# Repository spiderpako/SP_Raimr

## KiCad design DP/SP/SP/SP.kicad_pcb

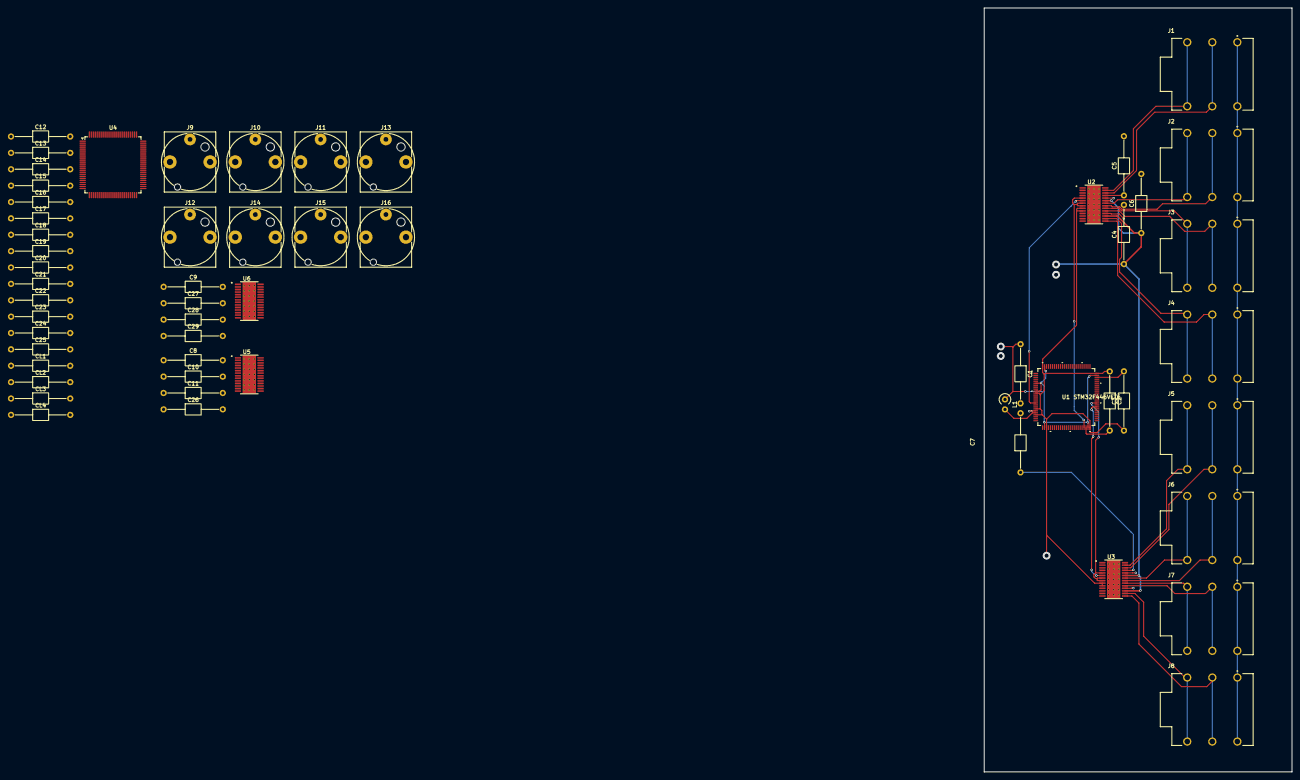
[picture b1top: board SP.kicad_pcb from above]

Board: 2 copper layers, 78.0 x 193.6 mm, 56 parts (0 on the bottom side), 60 nets.

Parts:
C1, C4, C6, C9, C10, C11, C12, C15, C16, C17, C18, C19, C20, C21, C23, C25, C26, C28, C29: 100n; C_Axial_L3.8mm_D2.6mm_P15.00mm_Horizontal
C2, C3, C13, C14: 4,7u; C_Axial_L3.8mm_D2.6mm_P15.00mm_Horizontal
C5, C7, C8, C27: 10u; C_Axial_L3.8mm_D2.6mm_P15.00mm_Horizontal
C22, C24: 1u; C_Axial_L3.8mm_D2.6mm_P15.00mm_Horizontal
CL1, CL2: 2p; C_Axial_L3.8mm_D2.6mm_P15.00mm_Horizontal
CL3, CL4: 10p; C_Axial_L3.8mm_D2.6mm_P15.00mm_Horizontal
J1, J2, J3, J4, J5, J6, J7, J8: NMJ6HCD2; NEUTRIK_NMJ6HCD2
J9, J10, J11, J12, J13, J14, J15, J16: NJ3FD-V; Jack_6.35mm_Neutrik_NJ3FD-V_Vertical
L1: 10u; L_Axial_L6.6mm_D2.7mm_P2.54mm_Vertical_Vishay_IM-2
U1: STM32F446VET6; LQFP100-14X14MM
U2, U3, U5, U6: PCM1681PWP; SOP65P640X120-29N
U4: STM32F446VETx; LQFP-100_14x14mm_P0.5mm

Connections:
+3.3V: C2.1, C3.1, C9.2, C10.2, C12.1, C15.1, C16.1, C17.1, C18.1, C19.1, C20.1, U1.11 (VDD_2), U1.19 (VDD_3), U1.22 (VDDA), U1.28 (VDD_4), U1.50 (VDD_5), U1.75 (VDD_6), U1.100 (VDD), U2.9 (VDD), U2.10 (DGND), U3.9 (VDD), U3.10 (DGND), U4.6 (VBAT), U4.11 (VDD), U4.19 (VDD), U4.28 (VDD), U4.50 (VDD), U4.75 (VDD), U4.100 (VDD), U5.9 (VDD), U6.9 (VDD)
+3.3VA: C1.1, L1.1, U1.6 (VBAT), U1.10 (VSS_2), U1.27 (VSS_3), U1.49 (VSS_4), U1.74 (VSS_5), U1.99 (VSS)
+5VA: C4.1, C6.1, C11.2, C26.2, C28.2, C29.2, U2.17 (VCC1), U2.23 (VCC2), U3.17 (VCC1), U3.23 (VCC2), U5.17 (VCC1), U5.23 (VCC2), U6.17 (VCC1), U6.23 (VCC2)
/1L: J1.T, J1.TN, U2.27 (VOUT1)
/1R: J1.R, J1.RN, U2.26 (VOUT2)
/2L: J2.T, J2.TN, U2.22 (VOUT3)
/2R: J2.R, J2.RN, U2.21 (VOUT4)
/3L: J3.T, J3.TN, U2.20 (VOUT5)
/3R: J3.R, J3.RN, U2.19 (VOUT6)
/4L: J4.T, J4.TN, U2.16 (VOUT7)
/4R: J4.R, J4.RN, U2.15 (VOUT8)
/5L: J5.T, J5.TN, U3.27 (VOUT1)
/5R: J5.R, J5.RN, U3.26 (VOUT2)
/6L: J6.T, J6.TN, U3.22 (VOUT3)
/6R: J6.R, J6.RN, U3.21 (VOUT4)
/7L: J7.T, J7.TN, U3.20 (VOUT5)
/7R: J7.R, J7.RN, U3.19 (VOUT6)
/8L: J8.T, J8.TN, U3.16 (VOUT7)
/8R: J8.R, J8.RN, U3.15 (VOUT8)
/NMJ6HCD2_2/5L: J12.T, U6.27 (VOUT1)
/NMJ6HCD2_2/5R: J12.R, U6.26 (VOUT2)
/NMJ6HCD2_2/6L: J14.T, U6.22 (VOUT3)
/NMJ6HCD2_2/6R: J14.R, U6.21 (VOUT4)
/NMJ6HCD2_2/7L: J15.T, U6.20 (VOUT5)
/NMJ6HCD2_2/7R: J15.R, U6.19 (VOUT6)
/NMJ6HCD2_2/8L: J16.T, U6.16 (VOUT7)
/NMJ6HCD2_2/8R: J16.R, U6.15 (VOUT8)
/PCM1681_1/BCK: U4.4 (PE5), U5.7 (BCK)
/PCM1681_1/DATA1: U4.5 (PE6), U5.6 (DATA1)
/PCM1681_1/LRCK: U4.3 (PE4), U5.8 (LRCK)
/PCM1681_1/SCK: U4.1 (PE2), U5.5 (SCK)
/PCM1681_2/BCK: U4.60 (PD13), U6.7 (BCK)
/PCM1681_2/DATA1: U4.58 (PD11), U6.6 (DATA1)
/PCM1681_2/LRCK: U4.59 (PD12), U6.8 (LRCK)
/PCM1681_2/SCK: U4.97 (PE0), U6.5 (SCK)
/SAI1_SCK_A: U1.47 (PB10), U2.5 (SCK), U2.7 (BCK), U2.8 (LRCK)
/SAI1_SD_A: U1.16 (PC1), U2.6 (DATA1)
/STM32F446VET6/OSC32_IN: CL1.2, U4.8 (PC14)
/STM32F446VET6/OSC32_OUT: CL2.2, U4.9 (PC15)
/STM32F446VET6/OSC_IN: CL3.2, U4.12 (PH0)
/STM32F446VET6/OSC_OUT: CL4.2, U4.13 (PH1)
Earth: J1.S, J1.SN, J2.S, J2.SN, J3.S, J3.SN, J4.S, J4.SN, J5.S, J5.SN, J6.S, J6.SN, J7.S, J7.SN, J8.S, J8.SN, J9.S, J10.S, J11.S, J12.S, J13.S, J14.S, J15.S, J16.S
GNDA: C1.2, C4.2, C5.2, C6.2, C7.2, C8.2, C11.1, C13.2, C14.2, C21.2, C22.2, C23.2, C24.2, C25.2, C26.1, C27.2, C28.1, C29.1, U1.20 (VSSA/VREF-), U2.18 (AGND1), U2.24 (AGND2), U3.18 (AGND1), U3.24 (AGND2), U4.20 (VSSA), U5.18 (AGND1), U5.24 (AGND2), U6.18 (AGND1), U6.24 (AGND2)
GNDD: C9.1, C10.1, C12.2, C15.2, C16.2, C17.2, C18.2, C19.2, C20.2, CL1.1, CL2.1, CL3.1, CL4.1, U4.10 (VSS), U4.27 (VSS), U4.49 (VSS), U4.74 (VSS), U4.99 (VSS), U5.10 (DGND), U6.10 (DGND)
NRST: C25.1, U4.14 (NRST)
unnamed: U1.58 (PD11), U3.6 (DATA1)
unnamed: U1.60 (PD13), U3.5 (SCK), U3.7 (BCK), U3.8 (LRCK)
unnamed: C2.2, U1.48 (VCAP_1)
unnamed: C3.2, U1.73 (VCAP_2)
unnamed: L1.2, U1.21 (VREF+)
unnamed: U2.29 (EXP), U2.29_1 (EXP), U2.29_2 (EXP), U2.29_3 (EXP), U2.29_4 (EXP), U2.29_5 (EXP), U2.29_6 (EXP), U2.29_7 (EXP), U2.29_8 (EXP), U2.29_9 (EXP), U2.29_10 (EXP), U2.29_11 (EXP), U2.29_12 (EXP), U2.29_13 (EXP), U2.29_14 (EXP), U2.29_15 (EXP), U2.29_16 (EXP), U2.29_17 (EXP), U2.29_18 (EXP), U2.29_19 (EXP), U2.29_20 (EXP), U2.29_21 (EXP)
unnamed: C5.1, U2.25 (VCOM)
unnamed: U3.29 (EXP), U3.29_1 (EXP), U3.29_2 (EXP), U3.29_3 (EXP), U3.29_4 (EXP), U3.29_5 (EXP), U3.29_6 (EXP), U3.29_7 (EXP), U3.29_8 (EXP), U3.29_9 (EXP), U3.29_10 (EXP), U3.29_11 (EXP), U3.29_12 (EXP), U3.29_13 (EXP), U3.29_14 (EXP), U3.29_15 (EXP), U3.29_16 (EXP), U3.29_17 (EXP), U3.29_18 (EXP), U3.29_19 (EXP), U3.29_20 (EXP), U3.29_21 (EXP)
unnamed: C7.1, U3.25 (VCOM)
unnamed: C13.1, U4.48 (VCAP_1)
unnamed: C14.1, U4.73 (VCAP_2)
unnamed: U5.29 (EXP), U5.29_1 (EXP), U5.29_2 (EXP), U5.29_3 (EXP), U5.29_4 (EXP), U5.29_5 (EXP), U5.29_6 (EXP), U5.29_7 (EXP), U5.29_8 (EXP), U5.29_9 (EXP), U5.29_10 (EXP), U5.29_11 (EXP), U5.29_12 (EXP), U5.29_13 (EXP), U5.29_14 (EXP), U5.29_15 (EXP), U5.29_16 (EXP), U5.29_17 (EXP), U5.29_18 (EXP), U5.29_19 (EXP), U5.29_20 (EXP), U5.29_21 (EXP)
unnamed: U6.29 (EXP), U6.29_1 (EXP), U6.29_2 (EXP), U6.29_3 (EXP), U6.29_4 (EXP), U6.29_5 (EXP), U6.29_6 (EXP), U6.29_7 (EXP), U6.29_8 (EXP), U6.29_9 (EXP), U6.29_10 (EXP), U6.29_11 (EXP), U6.29_12 (EXP), U6.29_13 (EXP), U6.29_14 (EXP), U6.29_15 (EXP), U6.29_16 (EXP), U6.29_17 (EXP), U6.29_18 (EXP), U6.29_19 (EXP), U6.29_20 (EXP), U6.29_21 (EXP)
VCOM: C8.1, C27.1, U5.25 (VCOM), U6.25 (VCOM)
VREF+: C21.1, C22.1, C23.1, C24.1, U4.21 (VREF+), U4.22 (VDDA)

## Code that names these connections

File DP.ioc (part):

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Mcu.Name=STM32F446V(C-E)Tx
Mcu.Package=LQFP100
Mcu.UserName=STM32F446VETx
PA0-WKUP.Signal=ADCx_IN0
PA1.Signal=ADCx_IN1
PA10.Mode=Asynchronous
PA10.Signal=USART1_RX
PA13.Mode=Serial_Wire
PA13.Signal=SYS_JTMS-SWDIO
PA14.Mode=Serial_Wire
PA14.Signal=SYS_JTCK-SWCLK
PA2.Signal=ADCx_IN2
PA3.Mode=OTG/Dual-Role-Device-HS
PA3.Signal=USB_OTG_HS_ULPI_D0
PA4.Mode=Half_Duplex_Master
PA4.Signal=I2S1_WS
PA5.Mode=OTG/Dual-Role-Device-HS
PA5.Signal=USB_OTG_HS_ULPI_CK
PA7.Mode=Half_Duplex_Master
PA7.Signal=I2S1_SD
PA9.Mode=Asynchronous
PA9.Signal=USART1_TX
PB0.Mode=OTG/Dual-Role-Device-HS
PB0.Signal=USB_OTG_HS_ULPI_D1
PB1.Mode=OTG/Dual-Role-Device-HS
PB1.Signal=USB_OTG_HS_ULPI_D2
PB10.Mode=OTG/Dual-Role-Device-HS
PB10.Signal=USB_OTG_HS_ULPI_D3
PB12.Mode=OTG/Dual-Role-Device-HS
PB12.Signal=USB_OTG_HS_ULPI_D5
PB13.Mode=OTG/Dual-Role-Device-HS
PB13.Signal=USB_OTG_HS_ULPI_D6
PB14.Mode=Full_Duplex_Master
PB14.Signal=SPI2_MISO
PB2.Mode=OTG/Dual-Role-Device-HS
PB2.Signal=USB_OTG_HS_ULPI_D4
PB3.Mode=Half_Duplex_Master
PB3.Signal=I2S1_CK
PB5.Mode=OTG/Dual-Role-Device-HS
PB5.Signal=USB_OTG_HS_ULPI_D7
PB6.Mode=I2C
PB6.Signal=I2C1_SCL
PB7.Mode=I2C
PB7.Signal=I2C1_SDA
PC0.Mode=OTG/Dual-Role-Device-HS
PC0.Signal=USB_OTG_HS_ULPI_STP
PC1.Mode=Full_Duplex_Master
PC1.Signal=SPI2_MOSI
PC10.Mode=SD_4_bits_Wide_bus
PC10.Signal=SDIO_D2
PC11.Mode=SD_4_bits_Wide_bus
PC11.Signal=SDIO_D3
PC12.Mode=SD_4_bits_Wide_bus
PC12.Signal=SDIO_CK
PC14-OSC32_IN.Mode=LSE-External-Oscillator
PC14-OSC32_IN.Signal=RCC_OSC32_IN
PC15-OSC32_OUT.Mode=LSE-External-Oscillator
PC15-OSC32_OUT.Signal=RCC_OSC32_OUT
PC2.Mode=OTG/Dual-Role-Device-HS
PC2.Signal=USB_OTG_HS_ULPI_DIR
PC3.Mode=OTG/Dual-Role-Device-HS
PC3.Signal=USB_OTG_HS_ULPI_NXT
PC4.Mode=Master_Clock_Activated
PC4.Signal=I2S1_MCK
PC7.Mode=Full_Duplex_Master
PC7.Signal=SPI2_SCK
PC8.Mode=SD_4_bits_Wide_bus
PC8.Signal=SDIO_D0
PC9.Mode=SD_4_bits_Wide_bus
PC9.Signal=SDIO_D1
PD11.Mode=SAI_A_MasterWithClock
PD11.Signal=SAI2_SD_A
PD12.Mode=SAI_A_MasterWithClock
PD12.Signal=SAI2_FS_A
PD13.Mode=SAI_A_MasterWithClock
PD13.Signal=SAI2_SCK_A
PD2.Mode=SD_4_bits_Wide_bus
PD2.Signal=SDIO_CMD
PD5.Mode=Asynchronous
PD5.Signal=USART2_TX
PD6.Mode=Asynchronous
PD6.Signal=USART2_RX
PE0.GPIOParameters=GPIO_Speed
PE0.GPIO_Speed=GPIO_SPEED_FREQ_VERY_HIGH
PE0.Mode=SAI_A_MasterWithClock
PE0.Signal=SAI2_MCLK_A
PE10.GPIOParameters=GPIO_PuPd,GPIO_Label,GPIO_ModeDefaultEXTI
PE10.GPIO_Label=VYBER_NAHORU
PE10.GPIO_ModeDefaultEXTI=GPIO_MODE_IT_FALLING
PE10.GPIO_PuPd=GPIO_PULLUP
PE10.Signal=GPXTI10
PE11.GPIOParameters=GPIO_PuPd,GPIO_Label,GPIO_ModeDefaultEXTI
PE11.GPIO_Label=VYBER_DOLU
PE11.GPIO_ModeDefaultEXTI=GPIO_MODE_IT_FALLING
PE11.GPIO_PuPd=GPIO_PULLUP
PE11.Signal=GPXTI11
PE12.GPIOParameters=GPIO_PuPd,GPIO_Label,GPIO_ModeDefaultEXTI
PE12.GPIO_Label=VRATIT_10S
PE12.GPIO_ModeDefaultEXTI=GPIO_MODE_IT_FALLING
PE12.GPIO_PuPd=GPIO_PULLUP
PE12.Signal=GPXTI12
PE13.GPIOParameters=GPIO_PuPd,GPIO_Label,GPIO_ModeDefaultEXTI
PE13.GPIO_Label=PRESKOCIT_10S
PE13.GPIO_ModeDefaultEXTI=GPIO_MODE_IT_FALLING
PE13.GPIO_PuPd=GPIO_PULLUP
PE13.Signal=GPXTI13
PE14.GPIOParameters=GPIO_PuPd,GPIO_Label,GPIO_ModeDefaultEXTI
PE14.GPIO_Label=POTVRDIT
PE14.GPIO_ModeDefaultEXTI=GPIO_MODE_IT_FALLING
PE14.GPIO_PuPd=GPIO_PULLUP
PE14.Signal=GPXTI14
PE2.GPIOParameters=GPIO_Speed
PE2.GPIO_Speed=GPIO_SPEED_FREQ_VERY_HIGH
PE2.Mode=SAI_A_MasterWithClock
PE2.Signal=SAI1_MCLK_A
PE4.Mode=SAI_A_MasterWithClock
PE4.Signal=SAI1_FS_A
PE5.Mode=SAI_A_MasterWithClock
PE5.Signal=SAI1_SCK_A
PE6.Mode=SAI_A_MasterWithClock
PE6.Signal=SAI1_SD_A
PH0-OSC_IN.Mode=HSE-External-Oscillator
PH0-OSC_IN.Signal=RCC_OSC_IN
PH1-OSC_OUT.Mode=HSE-External-Oscillator
PH1-OSC_OUT.Signal=RCC_OSC_OUT
RCC.HSE_VALUE=25000000
RCC.SYSCLKFreq_VALUE=50000000
RCC.SYSCLKSource=RCC_SYSCLKSOURCE_PLLCLK
board=custom

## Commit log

2025-11-25 Pridani schemat

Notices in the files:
parts and their libraries:
COPYRIGHT: Copyright (C) 2018 Accelerated Designs. All rights reserved
